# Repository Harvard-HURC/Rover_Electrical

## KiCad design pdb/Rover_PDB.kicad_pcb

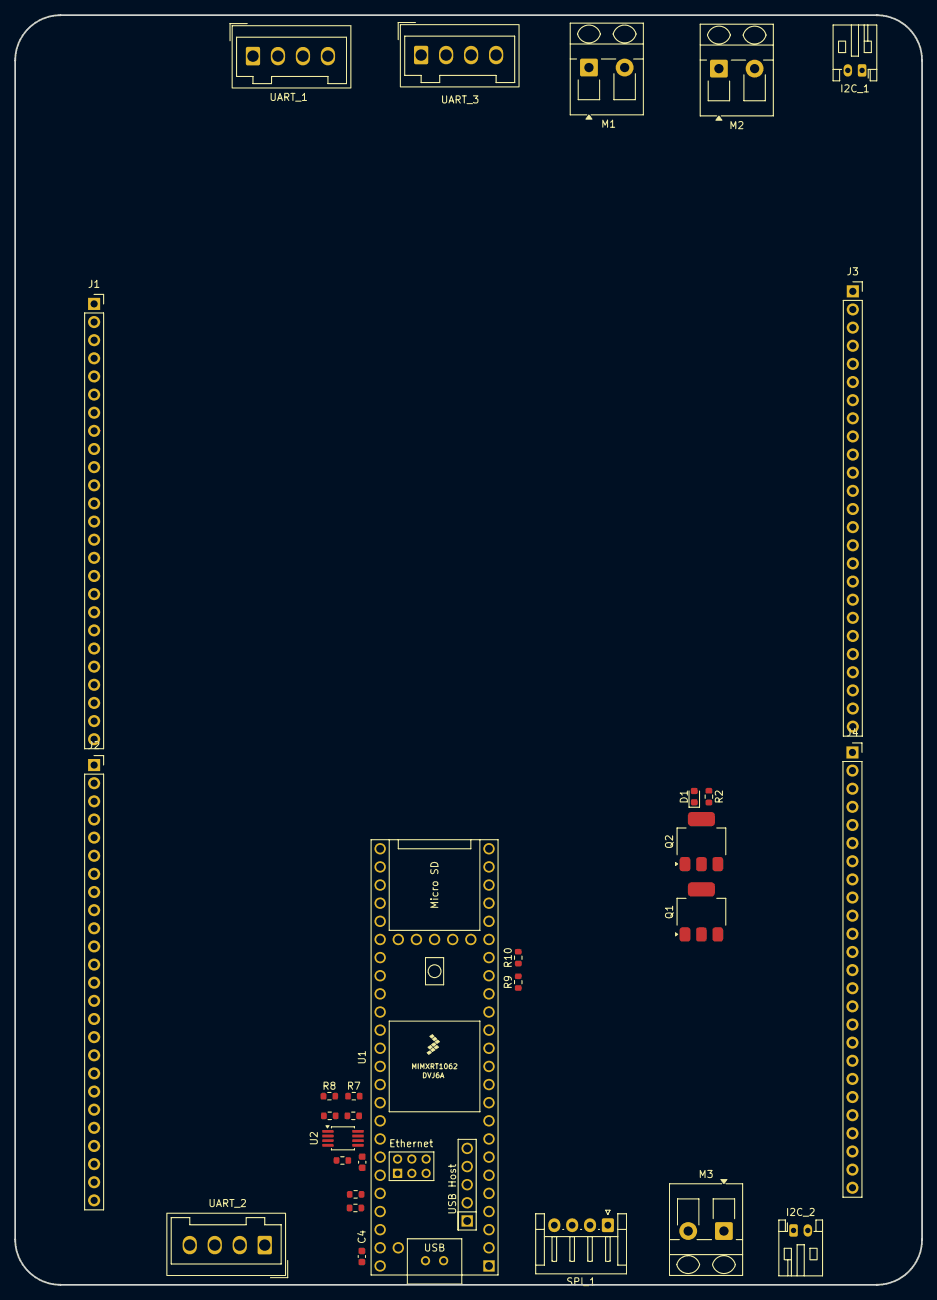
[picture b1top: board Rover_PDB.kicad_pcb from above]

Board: 2 copper layers, 127.0 x 177.8 mm, 30 parts (0 on the bottom side), 33 nets.

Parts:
C1: 0.2uF; C_0603_1608Metric
C4: 100nF; C_0603_1608Metric
D1: SS14; D_0603_1608Metric
I2C_1, I2C_2: Conn_01x02; JST_PH_S2B-PH-K_1x02_P2.00mm_Horizontal
J1, J2, J3, J4: Conn_01x25; PinSocket_1x25_P2.54mm_Vertical
M1, M2, M3: Fan; TerminalBlock_RND_205-00056_1x02_P5.00mm_45Degree
Q1, Q2: NMOS; SOT-223-3_TabPin2
R1: 1k; R_0603_1608Metric
R2, R6: 10k; R_0603_1608Metric
R3: 5k1; R_0603_1608Metric
R4, R5, R7, R8, R9, R10: 2k2; R_0603_1608Metric
SPI_1: Conn_01x04; JST_EH_S4B-EH_1x04_P2.50mm_Horizontal
U1: Teensy4.1; Teensy41
U2: MCP9808_MSOP; MSOP-8_3x3mm_P0.65mm
UART_1, UART_2, UART_3: Conn_01x04; Wago_734-134_1x04_P3.50mm_Vertical

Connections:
3V3: J2.1, J2.2, J2.3, J2.4, J2.5
5V: J2.6, J2.7, J2.8, J2.9, J2.10
12V: J2.11, J2.12, J2.13, J2.14, J2.15
24V: J2.16, J2.17, J2.18, J2.19, J2.20
+3V3: C1.1, R4.1, R5.1, R7.1, R8.1, R9.1, R10.1, U1.51 (3V3), U2.8 (V_{DD}), UART_1.1, UART_2.1, UART_3.1
+5V: C4.2, U1.48 (VIN)
+24V: D1.1 (K), M1.1 (+), M2.1 (+), M3.1 (+)
ADC: J4.6, J4.7, J4.8, J4.9, J4.10, J4.11, J4.12, J4.13, J4.14, J4.15
CS0: SPI_1.1, U1.12 (10_CS_MQSR)
GND: C1.2, C4.1, J1.1, J1.2, J1.3, J1.4, J1.5, J1.6, J1.7, J1.8, J1.9, J1.10, J1.11, J1.12, J1.13, J1.14, J1.15, J1.16, J1.17, J1.18, J1.19, J1.20, J1.21, J1.22, J1.23, J1.24, J1.25, J3.1, J3.2, J3.3, J3.4, J3.5, J3.6, J3.7, J3.8, J3.9, J3.10, J3.11, J3.12, J3.13, J3.14, J3.15, J3.16, J3.17, J3.18, J3.19, J3.20, J3.21, J3.22, J3.23, J3.24, J3.25, Q1.3 (S), Q2.3 (S), R3.2, R6.2, U1.1 (GND), U1.34 (GND), U1.47 (GND), U1.52 (GND), U1.58 (GND), U1.59 (GND), U1.64 (GND), U2.4 (GND), UART_1.2, UART_2.2, UART_3.2
MISO0: SPI_1.4, U1.14 (12_MISO_MQSL)
MOSI0: SPI_1.3, U1.13 (11_MOSI_CTX1)
unnamed: D1.2 (A), M1.2 (-), M2.2 (-), M3.2 (-), Q2.1 (D)
unnamed: Q1.1 (D), Q2.2 (G), R2.2
unnamed: Q1.2 (G), R1.2
unnamed: U1.2 (0_RX1_CRX2_CS1), UART_1.4
unnamed: U1.3 (1_TX1_CTX2_MISO1), UART_1.3
unnamed: U1.9 (7_RX2_OUT1A), UART_2.4
unnamed: U1.10 (8_TX2_IN1), UART_2.3
unnamed: R1.1, R6.1, U1.44 (22_A8_CTX1)
unnamed: U1.20 (28_RX7), UART_3.4
unnamed: U1.21 (29_TX7), UART_3.3
unnamed: R3.1, U2.5 (A2), U2.6 (A1), U2.7 (A0)
SCK0: SPI_1.2, U1.35 (13_SCK_LED)
SCL: J4.1, J4.2, J4.3, J4.4, J4.5
SCL_0: R5.2, U1.41 (19_A5_SCL), U2.2 (SCL)
SCL_1: I2C_1.1, R7.2, U1.38 (16_A2_RX4_SCL1)
SCL_2: I2C_2.1, R9.2, U1.16 (24_A10_TX6_SCL2)
SDA: J2.21, J2.22, J2.23, J2.24, J2.25
SDA_0: R4.2, U1.40 (18_A4_SDA), U2.1 (SDA)
SDA_1: I2C_1.2, R8.2, U1.39 (17_A3_TX4_SDA1)
SDA_2: I2C_2.2, R10.2, U1.17 (25_A11_RX6_SDA2)
UART: J4.16, J4.17, J4.18, J4.19, J4.20, J4.21, J4.22, J4.23, J4.24, J4.25

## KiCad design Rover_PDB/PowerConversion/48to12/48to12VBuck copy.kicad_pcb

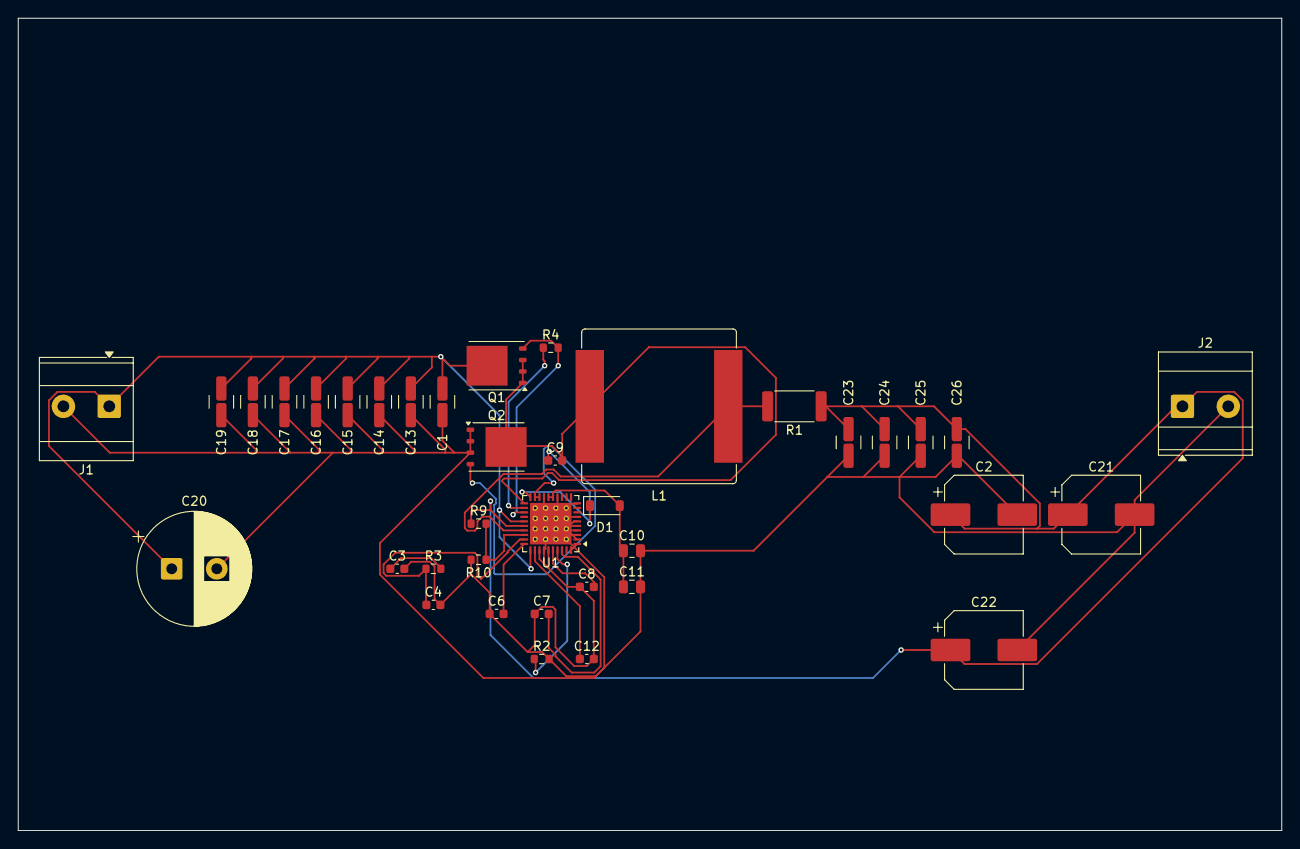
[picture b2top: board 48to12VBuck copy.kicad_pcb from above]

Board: 2 copper layers, 140.0 x 90.0 mm, 38 parts (0 on the bottom side), 18 nets.

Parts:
C1, C13, C14, C15, C16, C17, C18, C19: 10uF/100V; C_1210_3225Metric
C2, C21, C22: 220uF 25V; CP_Elec_8x10.5
C3: 4.7nF 50V C0G; C_0603_1608Metric
C4: 91pF 50V C0G; C_0603_1608Metric
C6: 100nF; C_0603_1608Metric
C7: 10nF; C_0603_1608Metric
C8: 470nF; C_0603_1608Metric
C9: 100nF 10V X7R; C_0603_1608Metric
C10, C11: 2.2uF; C_0805_2012Metric
C12: 470nF 10V X7R; C_0603_1608Metric
C20: 100uF 100V; CP_Radial_D12.5mm_P5.00mm
C23, C24, C25, C26: 47uF/25V; C_1210_3225Metric
D1: BAT46W 100V; D_SOD-123
J1: VIN 42-58V; TerminalBlock_Phoenix_MKDS-3-2-5.08_1x02_P5.08mm_Horizontal
J2: 12V OUT 10A; TerminalBlock_Phoenix_MKDS-3-2-5.08_1x02_P5.08mm_Horizontal
L1: 22uH SRP1770TA-220M; L_Bourns_SRP1770TA_16.9x16.9mm
Q1, Q2: CSD19531Q5A; TDSON-8-1
R1: 4.7mΩ 1% 2W; R_2512_6332Metric
R2: 220k 1% (100kHz); R_0603_1608Metric
R3: 35.7k 1%; R_0603_1608Metric
R4: 2.2Ω; R_0603_1608Metric
R9: 190k 1%; R_0603_1608Metric
R10: 10.0k 1%; R_0603_1608Metric
U1: LM5143QRHARQ1; Texas_RHA_VQFN-40-1EP_6x6mm_P0.5mm_EP4.6x4.6mm_ThermalVias

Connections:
FB1_0V6: R9.2, R10.1, U1.28
GND: C1.2, C2.2, C3.2, C4.2, C6.1, C7.1, C8.1, C10.2, C11.2, C12.2, C13.2, C14.2, C15.2, C16.2, C17.2, C18.2, C19.2, C20.2, C21.2, C22.2, C23.2, C24.2, C25.2, C26.2, J1.2, J2.2, Q2.1, Q2.2, Q2.3, R2.2, R10.2, U1.1, U1.2, U1.3, U1.4, U1.5, U1.6, U1.7, U1.10, U1.14, U1.17, U1.33, U1.34, U1.35, U1.40, U1.41
unnamed: C3.1, R3.2
unnamed: C10.1, C11.1, D1.2, U1.15, U1.16
unnamed: C9.1, D1.1, U1.20
unnamed: Q1.4, R4.2, U1.23
unnamed: C9.2, L1.2, Q1.1, Q1.2, Q1.3, Q2.5, U1.21
unnamed: Q2.4, U1.18, U1.19
unnamed: C4.1, R3.1, U1.29
unnamed: L1.1, R1.2, U1.27
unnamed: C7.2, U1.38
unnamed: R4.1, U1.22
unnamed: C12.1, U1.32
unnamed: R2.1, U1.37
unnamed: C6.2, U1.30
VDDA: C8.2, U1.36
VIN: C1.1, C13.1, C14.1, C15.1, C16.1, C17.1, C18.1, C19.1, C20.1, J1.1, Q1.5, U1.25, U1.31
VOUT: C2.1, C21.1, C22.1, C23.1, C24.1, C25.1, C26.1, J2.1, R1.1, R9.1, U1.26

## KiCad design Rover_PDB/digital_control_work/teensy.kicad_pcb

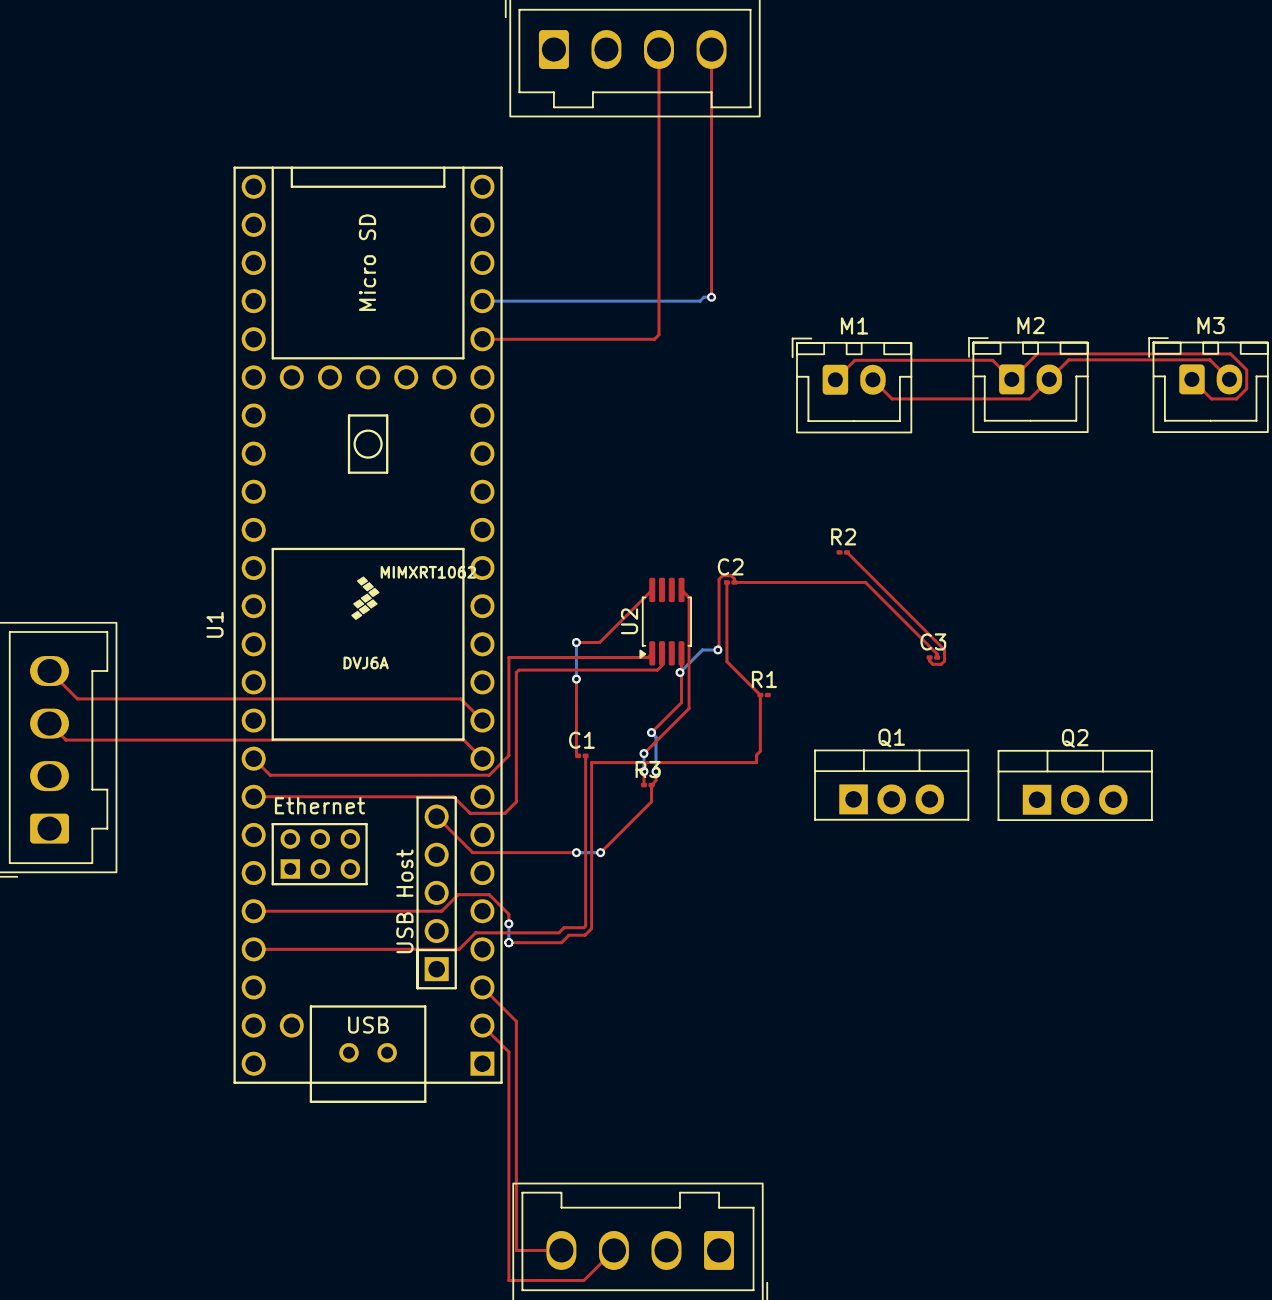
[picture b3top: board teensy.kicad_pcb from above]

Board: 2 copper layers, 16 parts (0 on the bottom side), 16 nets.

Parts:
C1: 0.2uF; C_01005_0402Metric
C2: 100nF; C_01005_0402Metric
C3: 50nF; C_01005_0402Metric
J1, J2, J3: Conn_01x04; Wago_734-134_1x04_P3.50mm_Vertical
M1, M2, M3: Fan; JST_XH_B2B-XH-A_1x02_P2.50mm_Vertical
Q1, Q2: NMOS; TO-220-3_Vertical
R1: 1k; R_01005_0402Metric
R2: 10k; R_01005_0402Metric
R3: 5k1; R_01005_0402Metric
U1: Teensy4.1; Teensy41
U2: MCP9808_MSOP; MSOP-8_3x3mm_P0.65mm

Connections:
GND: C2.2, C3.2, Q1.3 (S), Q2.3 (S), R3.2, U1.59 (GND), U2.4 (GND)
unnamed: J1.3, U1.2 (0_RX1_CRX2_CS1)
unnamed: J1.4, U1.3 (1_TX1_CTX2_MISO1)
unnamed: J2.3, U1.20 (28_RX7)
unnamed: J2.4, U1.21 (29_TX7)
unnamed: J3.3, U1.9 (7_RX2_OUT1A)
unnamed: J3.4, U1.10 (8_TX2_IN1)
unnamed: M1.1 (+), M2.1 (+), M3.1 (+)
unnamed: M1.2 (-), M2.2 (-), M3.2 (-), Q2.1 (D)
unnamed: C3.1, Q1.1 (D), Q2.2 (G), R2.2
unnamed: Q1.2 (G), R1.2
unnamed: C2.1, R1.1, U1.44 (22_A8_CTX1)
unnamed: C1.1, C1.2, U1.45 (23_A9_CRX1_MCLK1), U2.8 (V_{DD})
unnamed: R3.1, U2.5 (A2), U2.6 (A1), U2.7 (A0)
SCL_BMS_TEAM: U1.41 (19_A5_SCL), U2.2 (SCL)
SDA_BMS_TEAM: U1.40 (18_A4_SDA), U2.1 (SDA)
